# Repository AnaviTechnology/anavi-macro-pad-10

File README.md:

# ANAVI Macro Pad 10

**Open source programmable keypad with 9 mechanical switches and a rotary encoder.**

ANAVI Macro Pad 10 is an open source, custom-programmable, mini keyboard/keypad.

ANAVI Macro Pad 10 has been designed with [the cross platform and open source electronics design automation suite KiCad](https://kicad.org/). Compatible with [KMK firmware](https://github.com/KMKfw/kmk_firmware/tree/master/boards/anavi/macro-pad-10) and [QMK firmware](https://github.com/qmk/qmk_firmware/tree/master/keyboards/anavi).

[ANAVI Macro Pad 10, ANAVI Knob 1 and ANAVI Knobs 3 were brought to market through a crowdfunding campaign at Crowd Supply](https://www.crowdsupply.com/anavi-technology/anavi-macro-pad-10). For more details please visit https://anavi.technology/

# License

The project is released under the [Creative Commons Attribution-ShareAlike 4.0 International (CC BY-SA 4.0)](https://creativecommons.org/licenses/by-sa/4.0/).

Note: This is a human-readable summary of (and not a substitute for) the [license](https://creativecommons.org/licenses/by-sa/4.0/legalcode).

You are free to:

Share — copy and redistribute the material in any medium or format Adapt — remix, transform, and build upon the material for any purpose, even commercially. The licensor cannot revoke these freedoms as long as you follow the license terms. Under the following terms:

Attribution — You must give appropriate credit, provide a link to the license, and indicate if changes were made. You may do so in any reasonable manner, but not in any way that suggests the licensor endorses you or your use. ShareAlike — If you remix, transform, or build upon the material, you must distribute your contributions under the same license as the original. No additional restrictions — You may not apply legal terms or technological measures that legally restrict others from doing anything the license permits. Notices:

You do not have to comply with the license for elements of the material in the public domain or where your use is permitted by an applicable exception or limitation. No warranties are given. The license may not give you all of the permissions necessary for your intended use. For example, other rights such as publicity, privacy, or moral rights may limit how you use the material.

You will have to provide a link to the original creator of the project http://www.anavi.technology on any documentation or website.

Credit can be attributed through a link to the creator website: http://www.anavi.technology

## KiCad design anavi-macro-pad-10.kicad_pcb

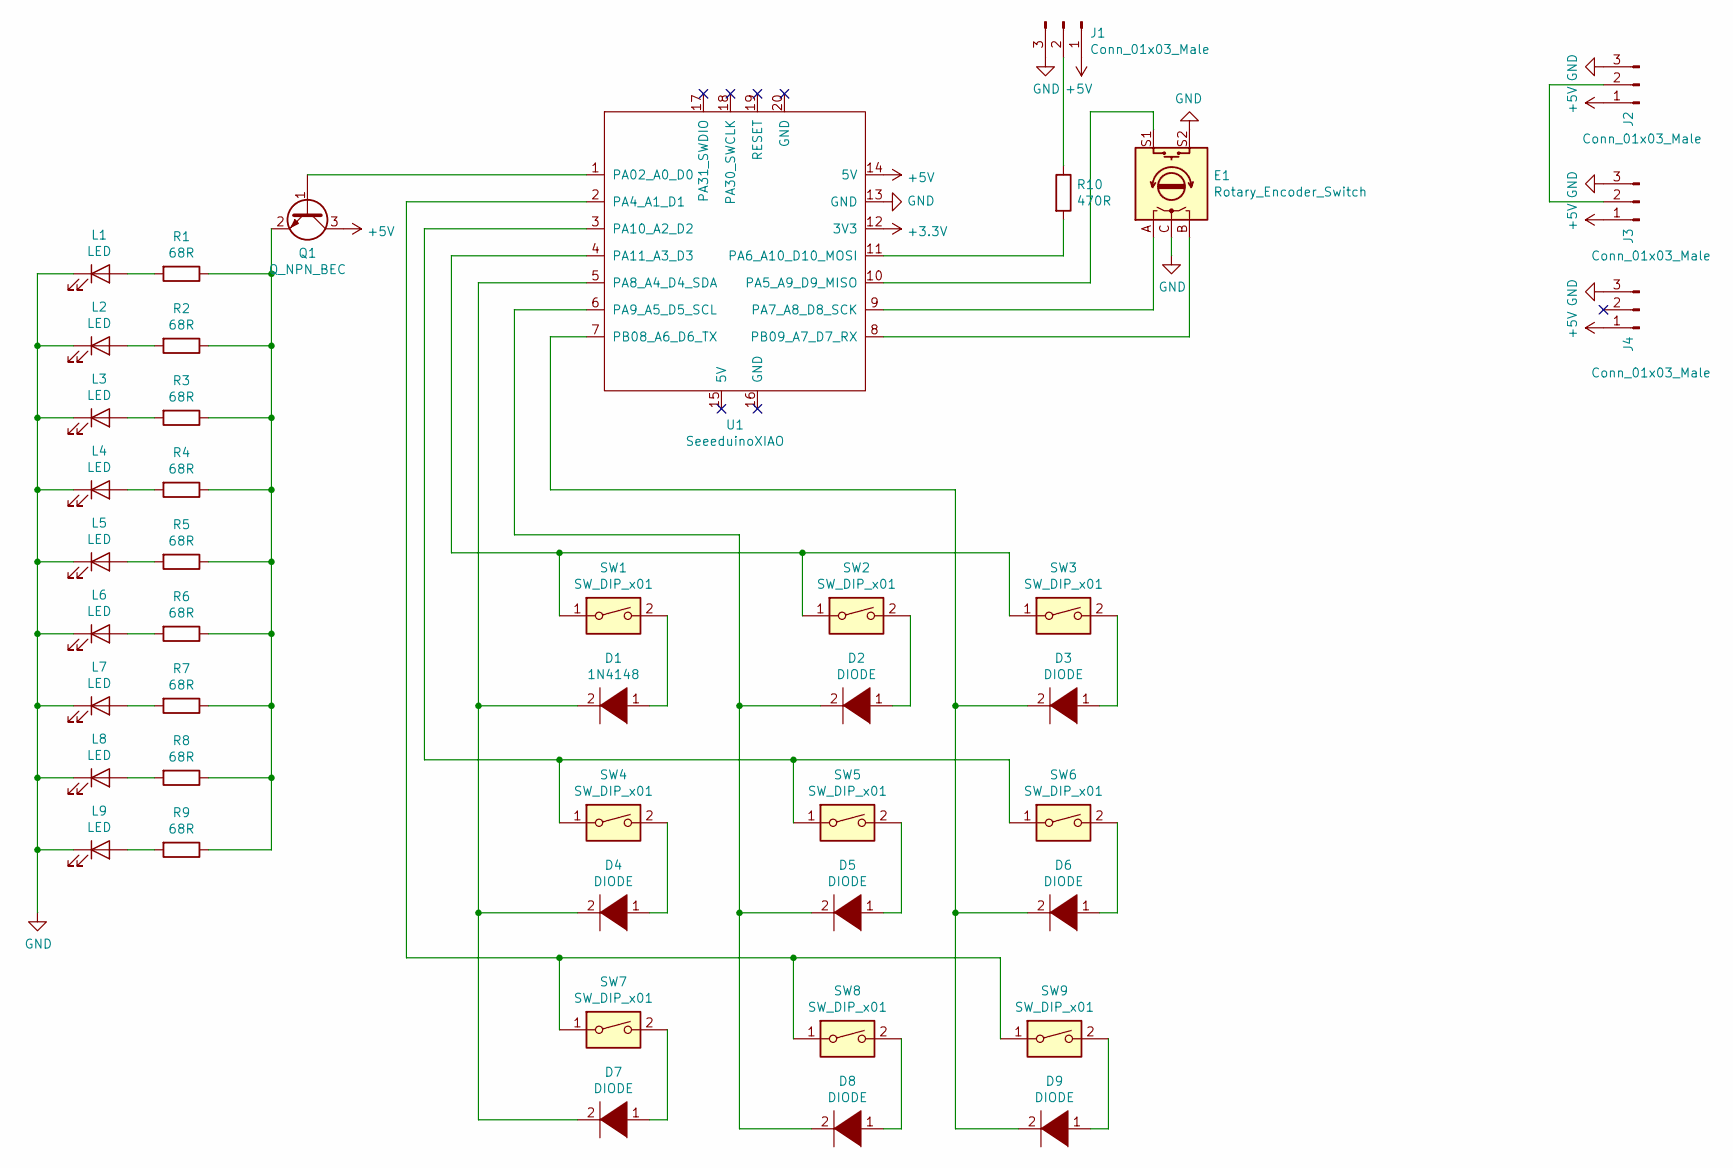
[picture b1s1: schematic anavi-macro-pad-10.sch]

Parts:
D1: 1N4148; D_SOD-123
D2, D3, D4, D5, D6, D7, D8, D9: DIODE; D_SOD-123
E1: Rotary_Encoder_Switch; RotaryEncoder_Alps_EC11E-Switch_Vertical_H20mm
J1, J2, J3, J4: Conn_01x03_Male; LedConnector_1x03_P2.54mm
L1, L2, L3, L4, L5, L6, L7, L8, L9: LED; LED_1206_3216Metric
Q1: Q_NPN_BEC; SOT-23
R1, R2, R3, R4, R5, R6, R7, R8, R9: 68R; R_0603_HandSoldering
R10: 470R; R_0603_HandSoldering
SW1, SW2, SW3, SW4, SW5, SW6, SW7, SW8, SW9: SW_DIP_x01; Kailh_socket_MX
U1: SeeeduinoXIAO; Seeeduino XIAO-MOUDLE14P-2.54-21X17.8MM

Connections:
+5V: J1.1, J2.1, J3.1, J4.1, Q1.3 (C), U1.14 (5V)
GND: E1.C, E1.S2, J1.3, J2.3, J3.3, J4.3, L1.1 (K), L2.1 (K), L3.1 (K), L4.1 (K), L5.1 (K), L6.1 (K), L7.1 (K), L8.1 (K), L9.1 (K), U1.13 (GND)
unnamed: D1.1 (K), SW1.2
unnamed: D1.2 (A), D4.2 (A), D7.2 (A), U1.5 (PA8_A4_D4_SDA)
unnamed: D2.1 (K), SW2.2
unnamed: D2.2 (A), D5.2 (A), D8.2 (A), U1.6 (PA9_A5_D5_SCL)
unnamed: D3.1 (K), SW3.2
unnamed: D3.2 (A), D6.2 (A), D9.2 (A), U1.7 (PB08_A6_D6_TX)
unnamed: D4.1 (K), SW4.2
unnamed: D5.1 (K), SW5.2
unnamed: D6.1 (K), SW6.2
unnamed: D7.1 (K), SW7.2
unnamed: D8.1 (K), SW8.2
unnamed: D9.1 (K), SW9.2
unnamed: E1.A, U1.9 (PA7_A8_D8_SCK)
unnamed: E1.B, U1.8 (PB09_A7_D7_RX)
unnamed: E1.S1, U1.10 (PA5_A9_D9_MISO)
unnamed: J1.2, R10.1
unnamed: J2.2, J3.2
unnamed: L1.2 (A), R1.2
unnamed: L2.2 (A), R2.2
unnamed: L3.2 (A), R3.2
unnamed: L4.2 (A), R4.2
unnamed: L5.2 (A), R5.2
unnamed: L6.2 (A), R6.2
unnamed: L7.2 (A), R7.2
unnamed: L8.2 (A), R8.2
unnamed: L9.2 (A), R9.2
unnamed: Q1.1 (B), U1.1 (PA02_A0_D0)
unnamed: Q1.2 (E), R1.1, R2.1, R3.1, R4.1, R5.1, R6.1, R7.1, R8.1, R9.1
unnamed: R10.2, U1.11 (PA6_A10_D10_MOSI)
unnamed: SW1.1, SW2.1, SW3.1, U1.4 (PA11_A3_D3)
unnamed: SW4.1, SW5.1, SW6.1, U1.3 (PA10_A2_D2)
unnamed: SW7.1, SW8.1, SW9.1, U1.2 (PA4_A1_D1)

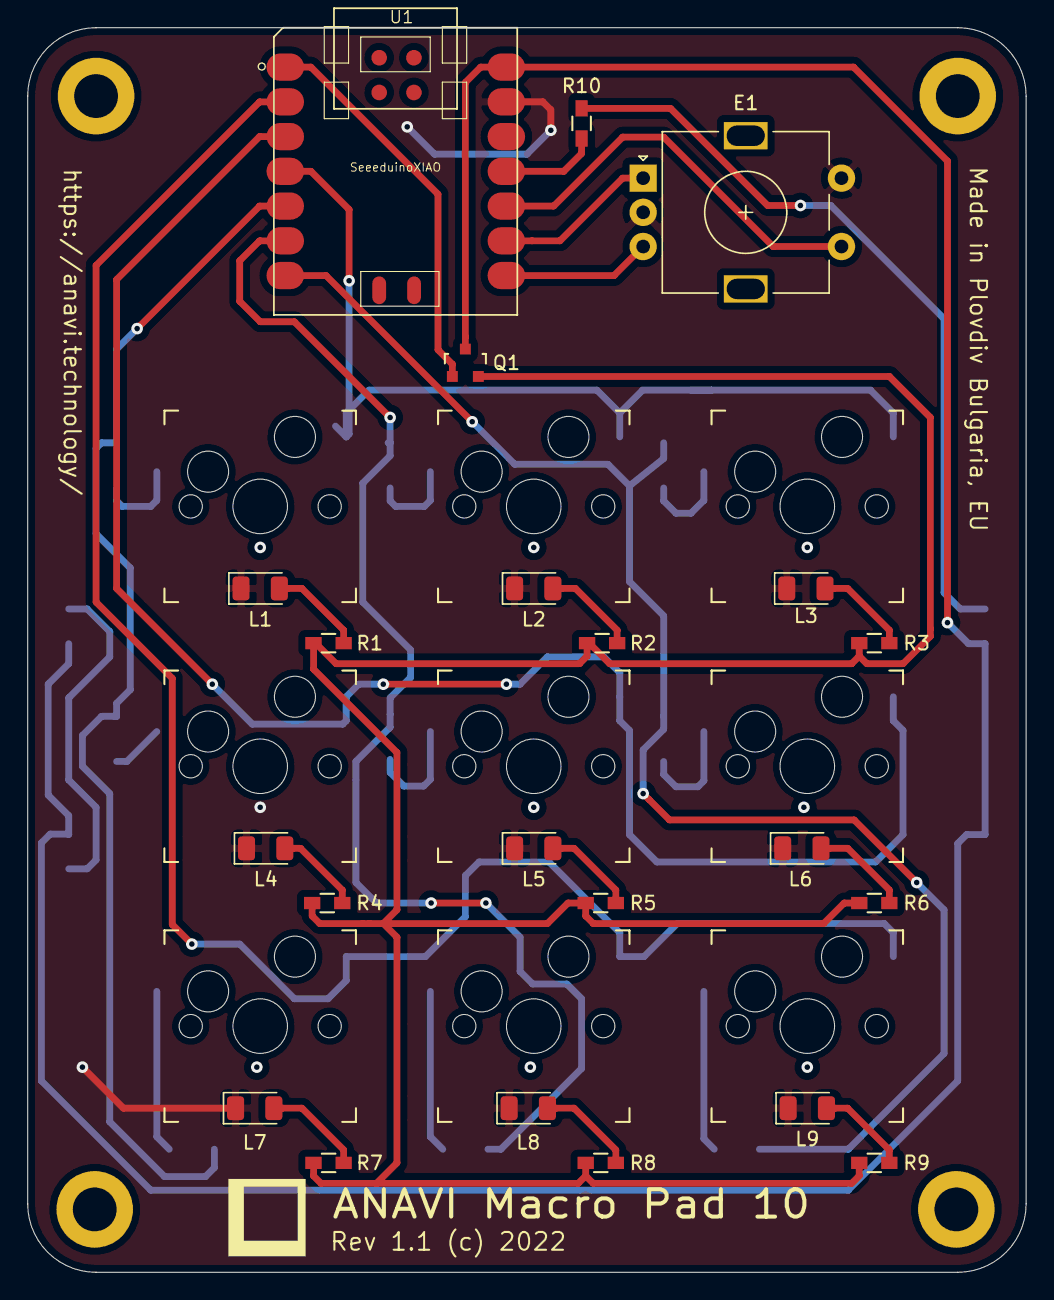
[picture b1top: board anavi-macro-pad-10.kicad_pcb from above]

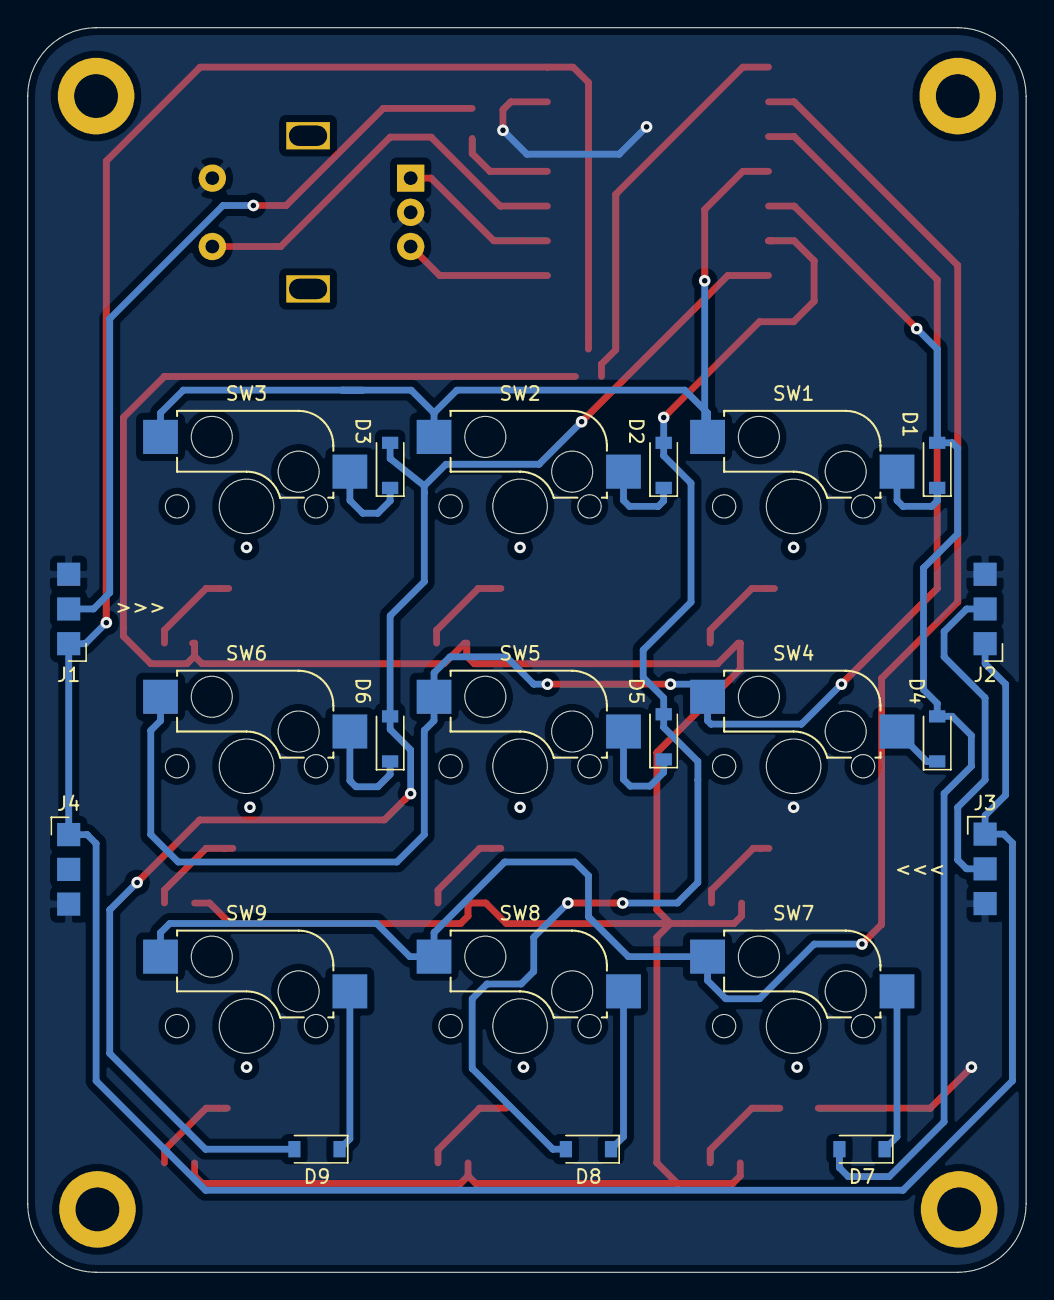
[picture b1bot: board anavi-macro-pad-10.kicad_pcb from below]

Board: 2 copper layers, 73.0 x 91.0 mm, 44 parts (13 on the bottom side), 34 nets.

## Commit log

2022-06-28 Initial commit
    ANAVI Macro Pad 10 work in progress.
2022-07-04 anavi-macro-pad-10.sch: Add LEDs
    Add LEDs for backlit and underlighting.
2022-07-06 components: Add LED and hot-swap connectors
    Add new components:
    - LED connector for WS2812B LED strips
    - Hot-swap connector for mechanical switches
2022-07-06 anavi-macro-pad-10: Create PCB
    Create printed circuit board.
2022-07-17 anavi-macro-pad-10.kicad_pcb: Finalize PCB
2022-07-22 anavi-macro-pad-10.kicad_pcb: Rev 1.1
    Rev 1.1 of ANAVI Macro Pad 10 with hardware fixes for the WS2812B
    LED strips.
2022-08-10 anavi-macro-pad-10.kicad_pcb: Enclosures
    Draw enclosures on the fabrication layer.
2022-10-09 README.md: Add anavi-macro-pad-10.jpg
    Add a photo of ANAVI Macro Pad 10 as well as more links.
2022-11-05 README.md: Add more details and a link
    Add more details and a link to the crowdfunding campaign.
2024-02-06 README.md: Fix KiCad URL
2025-07-30 case: Add STL and STEP files
    Include STL and STEP files for 3D printing a case for the ANAVI
    Macro Pad 10, designed by Pavlin Saksanov.
2025-08-02 case: Add keyboard spacer
    Add a keyboard spacer. Four of these should be placed between the
    printed circuit board and the bottom acrylic part when assembling
    together the 3D printed case for ANAVI Macro Pad 10.
2025-08-06 keyboard-spacer: Increase height to 1.7mm
    Increase height from 1.5mm to 1.7mm.
2025-11-30 anavi-macro-pad-10-bottom.scad: OpenSCAD
    The bottom part of ANAVI Macro Pad 10 3D printed case re-designed
    in OpenSCAD. Its dimensions were slightly increased to 97x78x20mm
    to account for 2 mm and 1 mm wall thicknesses.
2025-11-30 anavi-macro-pad-10-bottom.scad: Adjust top wall
    Adjust the height of the top wall to 3 mm.
2025-11-30 anavi-macro-pad-10-top.scad: OpenSCAD
    The top part of ANAVI Macro Pad 10 3D printed case re-designed
    in OpenSCAD. Its dimensions were slightly increased to 76x95x2.5mm
    to match the re-designed bottom part.

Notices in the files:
anavi-macro-pad-10.kicad_pcb:
Rev 1.1 (c) 2022
